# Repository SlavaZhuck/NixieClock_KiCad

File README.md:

# Clock on gas-discharge Nixie indicators  "IN-14" and Arduino
A fork of the adm503 project for those who want to be able to make changes to the circuit and/or board layout.
The circuit is copied with minimal changes (resistors, diode and transistor are changed to smd). The board and circuit are implemented in KiCad for 6 IN-14 lamps.<br>
The board has not been assembled and tested. It may not be. Please consider this information when using.<br>
The firmware has been updated to work with the DS3231M clock module.
The ability to automatically display data from the pressure, humidity and temperature sensor has been added.

Controls:
- When displaying the clock:
- M (double click) - enter the time settings mode;
- (hold) - enter the alarm settings mode;
- "minus" (short) - switches the lamp backlight modes;
- (hold) - enables/disables "glitches";
- "plus" (short) - switches the digit scrolling modes;
- (hold) - auto show temperature, pressure and humidity measurements
- sensor (short) - show temperature, pressure, humidity, set alarm time
(only if the alarm is on) and return to the clock display mode;
- (hold) - the same as (short).

- When the alarm goes off (a melody plays):
- sensor (short) - reset the signal, the alarm remains on;
- sensor (hold) - reset the signal, the alarm remains on.

- When displaying temperature, humidity, pressure, alarm time:
- sensor (short) - switch to the next parameter (pressure, humidity, set alarm time, clock display);
- (hold) - return to the clock display mode;

- When setting the time:
- M (short) - switch between setting hours and minutes;
- (hold) - reset the current group of digits to 00;
- "minus" (short) - decrease the value;
- (hold) - decrease the value by 5;
- "plus" (short) - increase the value;
- (hold) - increase the value by 5;
- sensor (short) - exit saving the settings;
- sensor (hold) - exit returning to the previous value.

- When setting the alarm:
- M (short) - switch between setting hours and minutes;
- (hold) - reset the current group of digits to 00;
- "minus" (short) - decrease the value;
- (hold) - decrease the value by 5;
- "plus" (short) - increase the value;
- (hold) - increase the value by 5;
- sensor (short) - exit with saving settings;
- sensor (hold) - turn on/off the alarm.

- Effects IN CLOCK MODE:
- Backlight (color changes cyclically: red, green, blue):
- Breathing;
- Constant glow;
- Disabled.
- Change digits (during change, the effect number is briefly displayed in all digits):
- (0) No effect;
- (1) Smooth fading;
- (2) Rewind in numerical order;
- (3) Rewind by cathodes;
- (4) Train;
- (5) Rubber band.
- The behavior of the second dot depends on whether the alarm is on? is set by the parameters:
- DOT_IN_TIME - when the alarm is off;
- DOT_IN_ALARM - when the alarm is on.
The dot behavior can be selected from the following values:
- DM_NULL, (0) the dot is always off;
- DM_ONCE, (1) the dot blinks once a second (normal);
- DM_HALF, (2) the dot changes brightness once a second;
- DM_TWICE, (3) the dot blinks twice a second;
- DM_THREE, (4) the dot blinks three times a second;
- DM_FULL, (5) the dot is always on

# Часы на газоразрядных индикаторах "ИН-14" и Arduino
Форк проекта adm503 для желающих иметь возможность сделать изменения в схеме и\или разводке платы.
Схема скопирована с минимальными изменениями (резисторы, диод и транзистор изменены на smd). Плата и схема реализованы в KiCad для 6-ти ламп ИН-14.<br>
Плата не была собрана и проверена. Возможно и не будет. Учитывайте пожалуйста эту информацию при использовании. <br>

Была обновлена прошивка для работы с модулем часов DS3231M.
Добавлена возможность автоматического показания данных с сенсора давления, влажности и температуры.
Управление:
  Управление:
  - При отображении часов:
    - М       (двойной клик) - войти в режим настроек времени;
    -         (удержание) - войти в режим настроек будильника;
    - "минус" (кратко) - переключает режимы подсветки ламп;
    -         (удержание) - включает/отключает "глюки";
    - "плюс"  (кратко) - переключает режимы перелистывания цифр;
    -         (удержание) - автопоказывать измерения температуры, давления и влажности
    - сенсор  (кратко) - показать температуру, давление, влажность, установленное время будильника
              (только если будильник включен) и вернуться в режим отображения часов;
    -         (удержание) - то же, что (кратко).
    
  - При срабатывании будильника (играет мелодия):
    - сенсор  (кратко) - сброс сигнала, будильник остаётся включенным;
    - сенсор  (удержание) - сброс сигнала, будильник остаётся включенным.
    
  - При демонстрации температуры, влажности, давлении, времени будильника:
    - сенсор  (кратко) - переключиться на следующий параметр (давление, влажность, установленное
              время будильника, отображение часов);
    -         (удержание) - вернуться в режим отображения часов;
    
  - При настройке времени:
    - М       (кратко) - переключение между установкой часов и минут;
    -         (удержание) - сброс текущей группы разрядов в 00;
    - "минус" (кратко) - уменьшение значения;
    -         (удержание) - уменьшение значения на 5;
    - "плюс"  (кратко) - увеличение значения;
    -         (удержание) - уведичение значения на 5;
    - сенсор  (кратко) - выход с сохранением установок;
    - сенсор  (удержание) - выход с возвратом к прежнему значению.
    
  - При настройке будильника:
    - М       (кратко) - переключение между установкой часов и минут;
    -         (удержание) - сброс текущей группы разрядов в 00;
    - "минус" (кратко) - уменьшение значения;
    -         (удержание) - уменьшение значения на 5;
    - "плюс"  (кратко) - увеличение значения;
    -         (удержание) - уведичение значения на 5;
    - сенсор  (кратко) - выход с сохранением установок;
    - сенсор  (удержание) - включение/выключение будильника.
    
  - Эффекты В РЕЖИМЕ ЧАСОВ:
    - Подсветка (циклически изменяется цвет: красный,  зелёный, синий):
      - Дыхание;
      - Постоянное свечение;
      - Отключена.
    - Смена цифр (при смене на короткое время отображается номер эффекта во всех разрядах):
      - (0) Без эффекта;
      - (1) Плавное угасание;
      - (2) Перемотка по порядку числа;
      - (3) Перемотка по катодам;
      - (4) Поезд;
      - (5) Резинка.
    - Поведение секундной точки зависит от того, включен ли будильник? устанавливается параметрами:
      - DOT_IN_TIME - когда будильник выключен;
      - DOT_IN_ALARM - когда будильник включен.
      Выбор поведения точки можно осуществлять из следующих величин:
      - DM_NULL, (0) точка постоянно выключена;
      - DM_ONCE, (1) точка моргает один раз в секунду (штатно);
      - DM_HALF, (2) точка изменяет яркость раз в секунду;
      - DM_TWICE,(3) точка моргает два раза в секунду;
      - DM_THREE,(4) точка моргает три раза в секунду;
      - DM_FULL, (5) точка постоянно включена

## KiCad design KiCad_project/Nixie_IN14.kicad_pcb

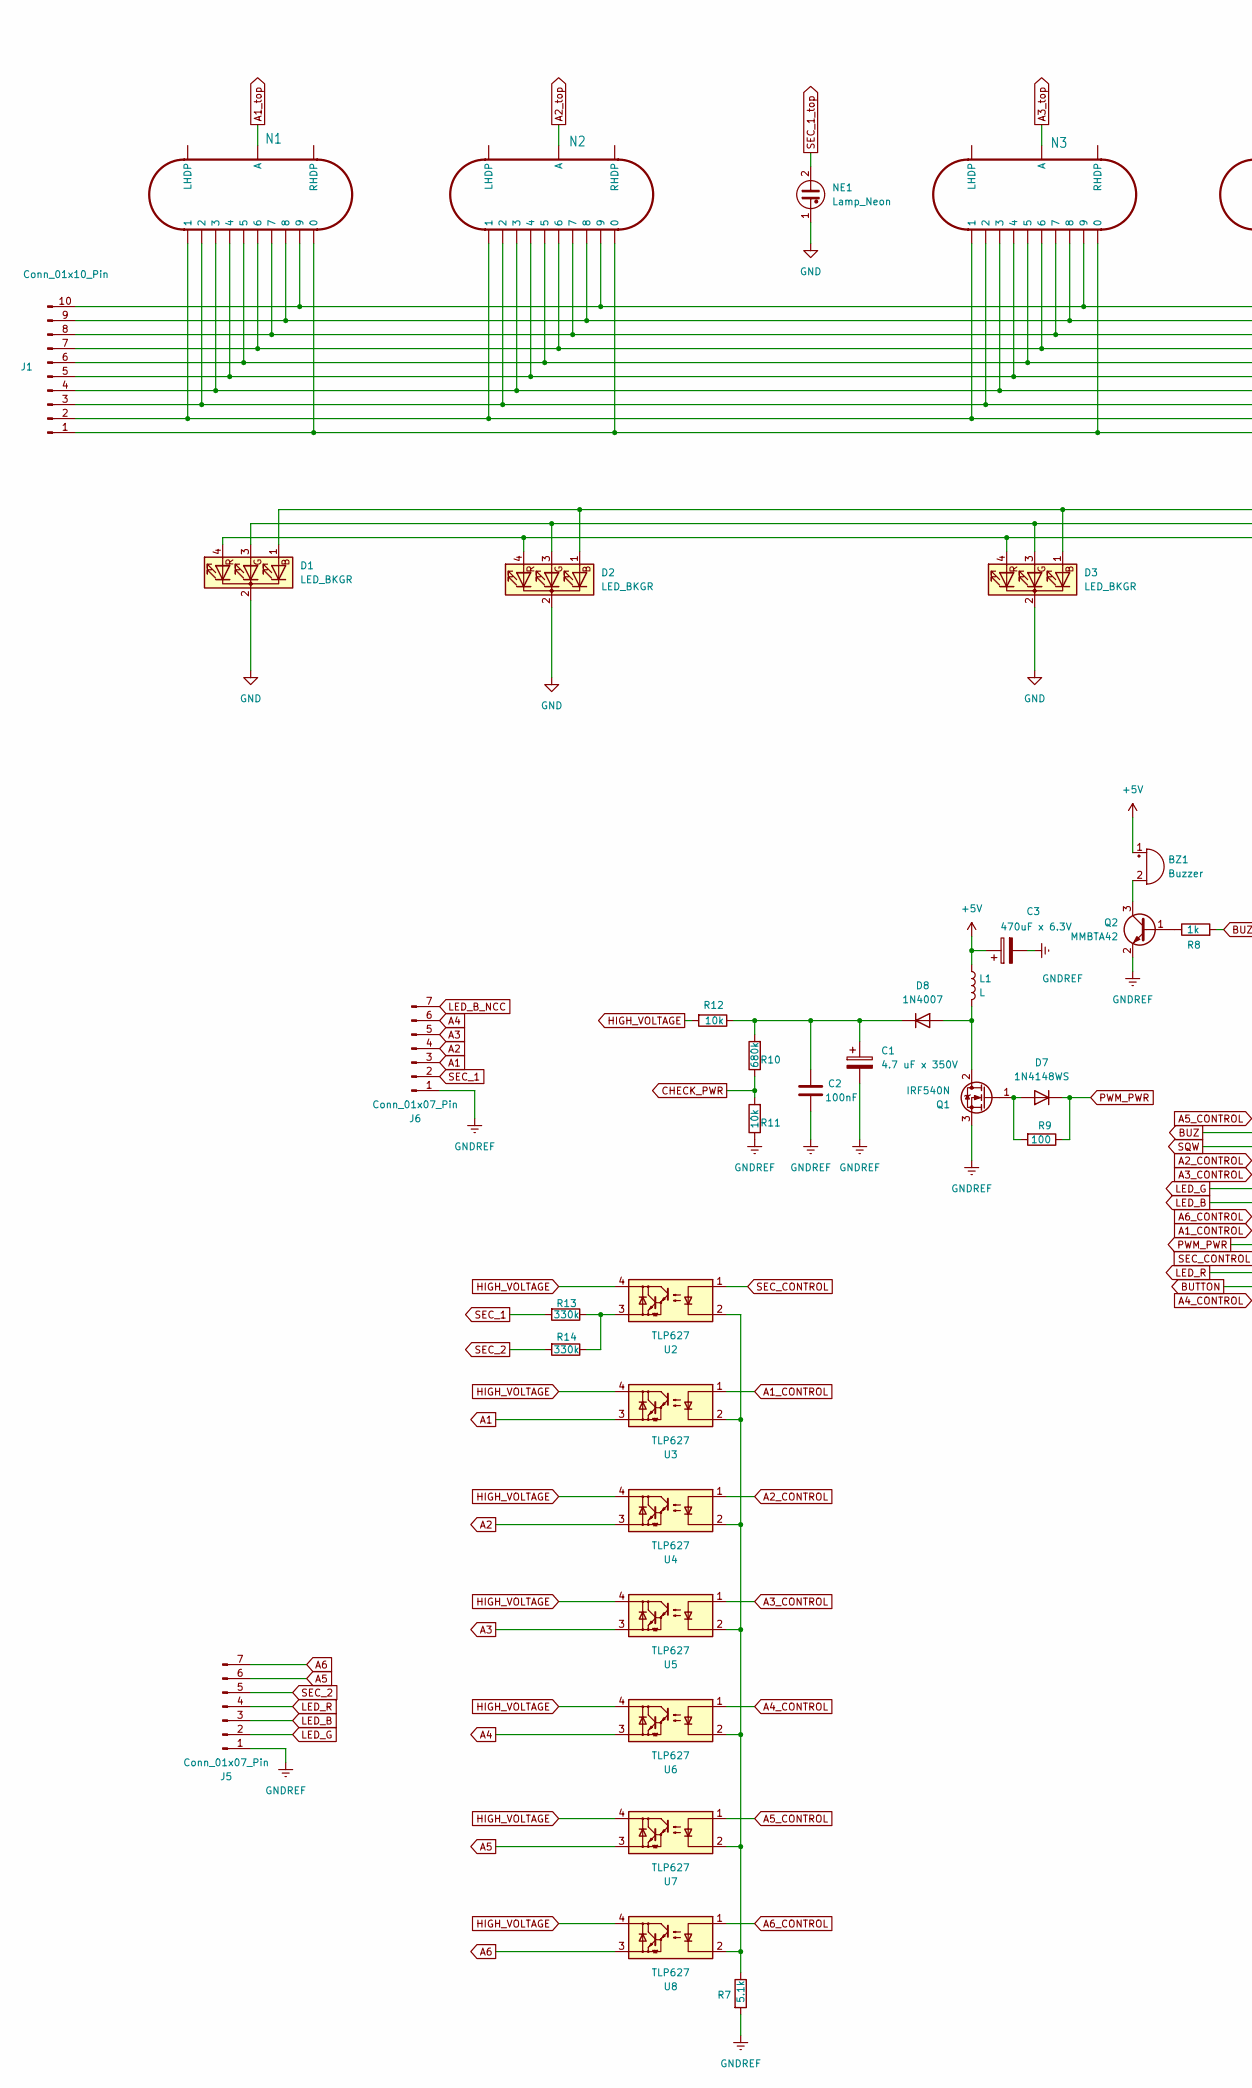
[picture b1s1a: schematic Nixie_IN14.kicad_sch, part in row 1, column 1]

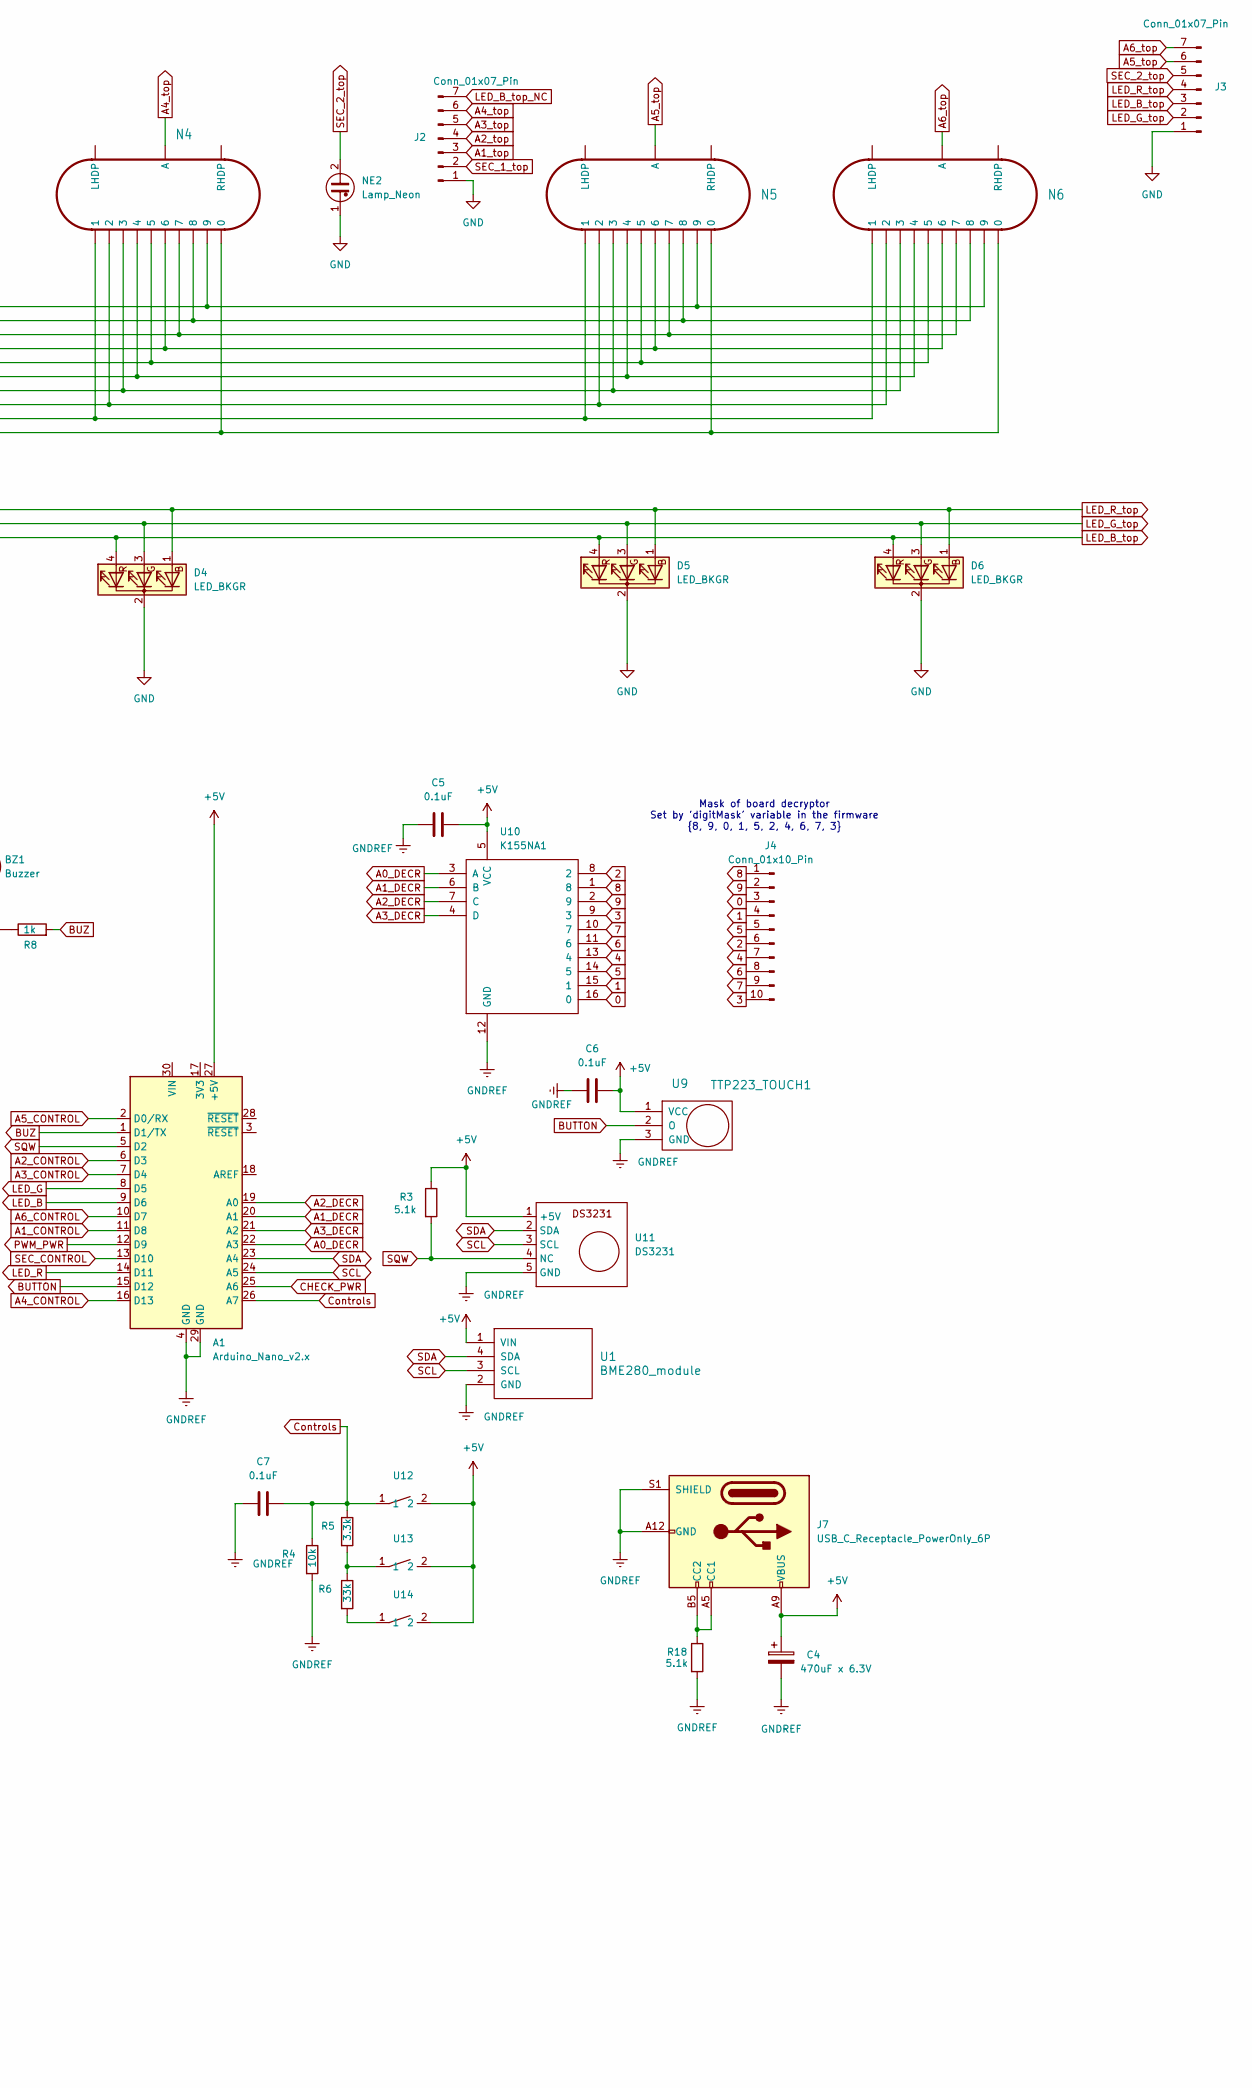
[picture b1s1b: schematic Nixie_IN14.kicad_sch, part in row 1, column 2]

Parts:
A1: Arduino_Nano_v2.x; Arduino_Nano
BZ1: Buzzer; Buzzer_TDK_PS1240P02BT_D12.2mm_H6.5mm
C1: 4.7 uF x 350V; CP_Radial_D10.0mm_P2.50mm_P5.00mm
C2: 100nF; C_Rect_L10.0mm_W5.0mm_P5.00mm_P7.50mm
C3, C4: 470uF x 6.3V; CP_Radial_D5.0mm_P2.50mm
C5, C6, C7: 0.1uF; C_1206_3216Metric
D1, D2, D3, D4, D5, D6: LED_BKGR; LED_D5.0mm-4_RGB
D7: 1N4148WS; D_SOD-323
D8: 1N4007; D_DO-41_SOD81_P7.62mm_Horizontal
J1: Conn_01x10_Pin; PinSocket_1x10_P2.54mm_Vertical
J2, J3: Conn_01x07_Pin; PinSocket_1x07_P2.54mm_Vertical
J4: Conn_01x10_Pin; PinHeader_1x10_P2.54mm_Vertical
J5, J6: Conn_01x07_Pin; PinHeader_1x07_P2.54mm_Vertical
J7: USB_C_Receptacle_PowerOnly_6P; USB_C_Receptacle_HRO_TYPE-C-31-M-17
L1: L; L_Radial_D10.0mm_P5.00mm_Fastron_07M
N1, N2, N3, N4, N5, N6: IN-14
NE1, NE2: Lamp_Neon; NE2-NEON-BULB-DRILL
Q1: IRF540N; TO-220-3_Vertical
Q2: MMBTA42; SOT-23
R3, R7, R18: 5.1k; R_1206_3216Metric_Pad1.30x1.75mm_HandSolder
R4, R11, R12: 10k; R_1206_3216Metric_Pad1.30x1.75mm_HandSolder
R5: 3.3k; R_1206_3216Metric_Pad1.30x1.75mm_HandSolder
R6: 33k; R_1206_3216Metric_Pad1.30x1.75mm_HandSolder
R8: 1k; R_1206_3216Metric_Pad1.30x1.75mm_HandSolder
R9: 100; R_1206_3216Metric_Pad1.30x1.75mm_HandSolder
R10: 680k; R_1206_3216Metric_Pad1.30x1.75mm_HandSolder
R13, R14: 330k; R_1206_3216Metric_Pad1.30x1.75mm_HandSolder
U1: BME280_module
U2, U3, U4, U5, U6, U7, U8: TLP627; DIP-4_W7.62mm
U9: TTP223_TOUCH1; PinHeader_1x03_P2.54mm_Vertical
U10: K155NA1; DIP-16_W7.62mm
U11: DS3231; DS3231_PI
U12, U13, U14: my_button

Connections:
0: J4.3, U10.16 (0)
1: J4.4, U10.15 (1)
2: J4.6, U10.8 (2)
3: J4.10, U10.9 (3)
4: J4.7, U10.13 (4)
5: J4.5, U10.14 (5)
6: J4.8, U10.11 (6)
7: J4.9, U10.10 (7)
8: J4.1, U10.1 (8)
9: J4.2, U10.2 (9)
+5V: A1.27 (+5V), BZ1.1 (+), C3.1, C4.1, C5.2, C6.2, J7.A9 (VBUS), J7.B9 (VBUS), L1.1, R3.1, U1.1 (VIN), U9.1 (VCC), U10.5 (VCC), U11.1 (+5V), U12.2, U13.2, U14.2
A0_DECR: A1.22 (A3), U10.3 (A)
A1: J6.3, U3.3
A1_CONTROL: A1.11 (D8), U3.1
A1_DECR: A1.20 (A1), U10.6 (B)
A1_top: J2.3, N1.A
A2: J6.4, U4.3
A2_CONTROL: A1.6 (D3), U4.1
A2_DECR: A1.19 (A0), U10.7 (C)
A2_top: J2.4, N2.A
A3: J6.5, U5.3
A3_CONTROL: A1.7 (D4), U5.1
A3_DECR: A1.21 (A2), U10.4 (D)
A3_top: J2.5, N3.A
A4: J6.6, U6.3
A4_CONTROL: A1.16 (D13), U6.1
A4_top: J2.6, N4.A
A5: J5.6, U7.3
A5_CONTROL: A1.2 (D0/RX), U7.1
A5_top: J3.6, N5.A
A6: J5.7, U8.3
A6_CONTROL: A1.10 (D7), U8.1
A6_top: J3.7, N6.A
BUTTON: A1.15 (D12), U9.2 (O)
BUZ: A1.1 (D1/TX), R8.2
CHECK_PWR: A1.25 (A6), R10.1, R11.2
Controls: A1.26 (A7), C7.1, R4.1, R5.1, U12.1
GND: D1.2 (K), D2.2 (K), D3.2 (K), D4.2 (K), D5.2 (K), D6.2 (K), J2.1, J3.1, NE1.1, NE2.1
GNDREF: A1.4 (GND), A1.29 (GND), C1.2, C2.2, C3.2, C4.2, C5.1, C6.1, C7.2, J5.1, J6.1, J7.A12 (GND), J7.B12 (GND), J7.S1 (SHIELD), Q1.3 (S), Q2.2 (E), R4.2, R7.2, R11.1, R18.2, U1.2 (GND), U9.3 (GND), U10.12 (GND), U11.5 (GND)
HIGH_VOLTAGE: R12.2, U2.4, U3.4, U4.4, U5.4, U6.4, U7.4, U8.4
LED_B: A1.9 (D6), J5.3
LED_B_NCC: J6.7
LED_B_top: D1.4 (RA), D2.4 (RA), D3.4 (RA), D4.4 (RA), D5.4 (RA), D6.4 (RA), J3.3
LED_B_top_NC: J2.7
LED_G: A1.8 (D5), J5.2
LED_G_top: D1.3 (GA), D2.3 (GA), D3.3 (GA), D4.3 (GA), D5.3 (GA), D6.3 (GA), J3.2
LED_R: A1.14 (D11), J5.4
LED_R_top: D1.1 (BA), D2.1 (BA), D3.1 (BA), D4.1 (BA), D5.1 (BA), D6.1 (BA), J3.4
unnamed: BZ1.2 (-), Q2.3 (C)
unnamed: D7.2 (A), Q1.1 (G), R9.2
unnamed: D8.2 (A), L1.2, Q1.2 (D)
unnamed: C1.1, C2.1, D8.1 (K), R10.2, R12.1
unnamed: J1.1, N1.0, N2.0, N3.0, N4.0, N5.0, N6.0
unnamed: J1.2, N1.1, N2.1, N3.1, N4.1, N5.1, N6.1
unnamed: J1.3, N1.2, N2.2, N3.2, N4.2, N5.2, N6.2
unnamed: J1.4, N1.3, N2.3, N3.3, N4.3, N5.3, N6.3
unnamed: J1.5, N1.4, N2.4, N3.4, N4.4, N5.4, N6.4
unnamed: J1.6, N1.5, N2.5, N3.5, N4.5, N5.5, N6.5
unnamed: J1.7, N1.6, N2.6, N3.6, N4.6, N5.6, N6.6
unnamed: J1.8, N1.7, N2.7, N3.7, N4.7, N5.7, N6.7
unnamed: J1.9, N1.8, N2.8, N3.8, N4.8, N5.8, N6.8
unnamed: J1.10, N1.9, N2.9, N3.9, N4.9, N5.9, N6.9
unnamed: J7.A5 (CC1), J7.B5 (CC2), R18.1
unnamed: Q2.1 (B), R8.1
unnamed: R5.2, R6.1, U13.1
unnamed: R6.2, U14.1
unnamed: R7.1, U2.2, U3.2, U4.2, U5.2, U6.2, U7.2, U8.2
unnamed: R13.1, R14.1, U2.3
PWM_PWR: A1.12 (D9), D7.1 (K), R9.1
SCL: A1.24 (A5), U1.3 (SCL), U11.3 (SCL)
SDA: A1.23 (A4), U1.4 (SDA), U11.2 (SDA)
SEC_1: J6.2, R13.2
SEC_1_top: J2.2, NE1.2
SEC_2: J5.5, R14.2
SEC_2_top: J3.5, NE2.2
SEC_CONTROL: A1.13 (D10), U2.1
SQW: A1.5 (D2), R3.2, U11.4 (NC)

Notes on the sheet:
Mask of board decryptor Set by 'digitMask' variable in the firmware {8, 9, 0, 1, 5, 2, 4, 6, 7, 3}

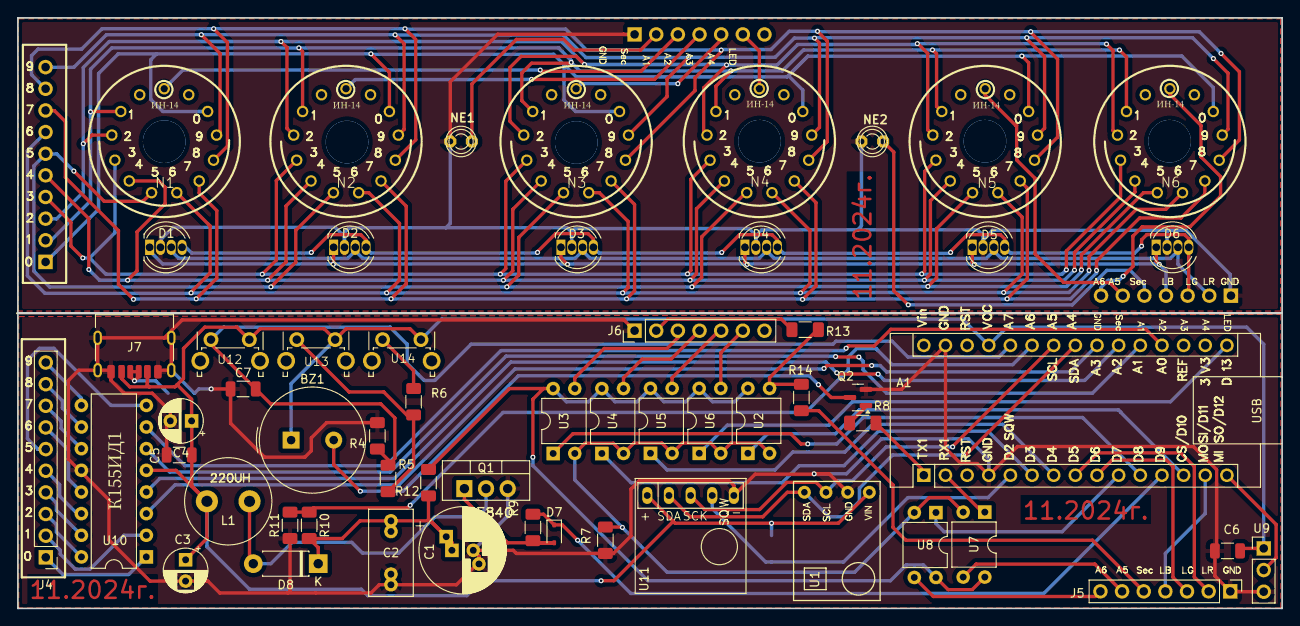
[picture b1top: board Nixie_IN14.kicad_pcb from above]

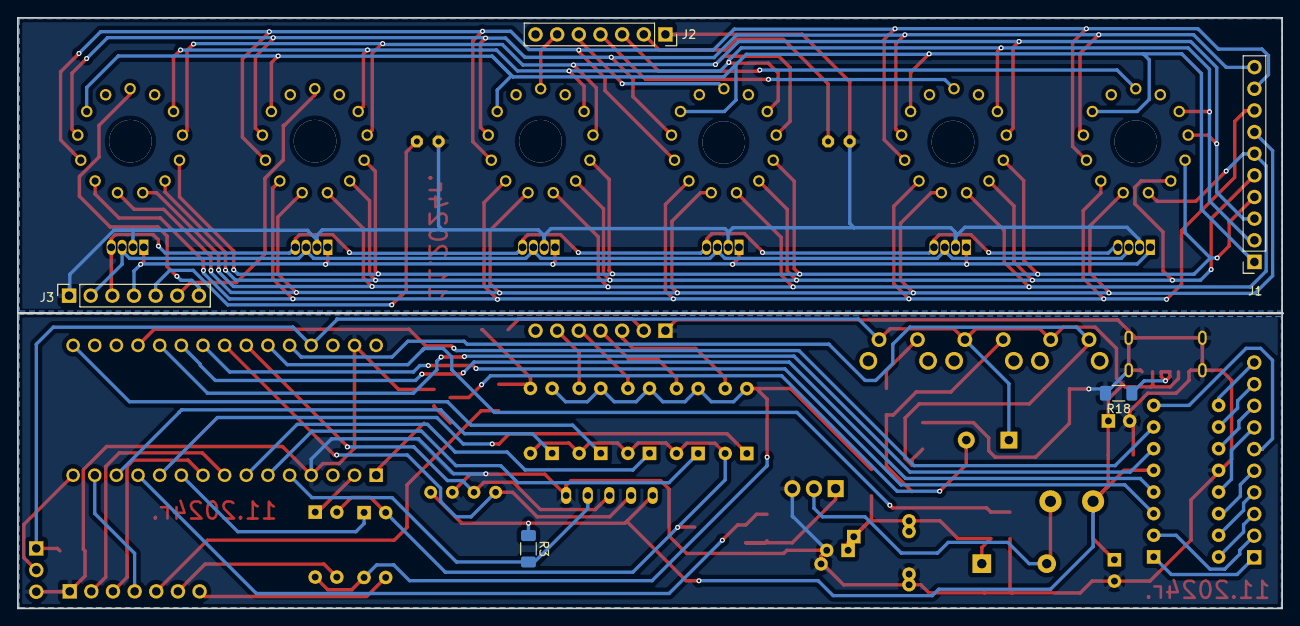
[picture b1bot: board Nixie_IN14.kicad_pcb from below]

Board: 2 copper layers, 148.3 x 69.3 mm, 62 parts (5 on the bottom side), 75 nets.

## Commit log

2021-10-11 Update LICENSE
2024-09-16 upload KiCad libraries PCB routing is not finished
2024-09-16 added missing lib
2024-09-16 added missed power capacitors fixed some resistor values continue placing elements on the PCB
2024-09-17 continue placing components
2024-09-17 placing and routing update
2024-09-18 optimized placement for tracing added labels on schematic added capacitor for button
2024-09-18 updated placement started routing
2024-09-19 placeng update first version of tracing is finished
2024-09-19 optimized routing and placement
2024-09-19 optimized placement and routing
2024-09-20 increased via diameters for drilling, routing optimization
2024-09-20 added 3d models
2024-09-21 placed transistors instead of optic pairs
2024-09-21 fixed connection error replaced and rerouted
2024-09-22 minor routing optimization
2024-09-22 added power keys for LEDs resistor pacjakges changed from 0805 to 1206
2024-11-02 DS3231SN switched to DS3231M,
    left only type 3 board support
2024-11-02 added periodic autoshow measurements with control from R-button (hold to turn On-Off) with saving to EEPROM
2024-11-06 decreased Voltage to 170 Volts, minor changes of brightness. Changed synchro mechanism for dynamic indication
2024-11-07 Added VScode project in "PlatformIO" extention
2024-11-08 git-annex in slava@slava-ThinkPad-E14-Gen-4-M:~/Documents/NixieClock_KiCad
2024-11-08 restored broken commit = updated placing of Arduino on PCB, optimized routing
2024-11-19 returned to D3231SN increased DOT brightness
2024-12-03 fixed compiler warnings updated time update process, each second data read from RTC updated auto show of measurements
2024-12-03 moved variable auto_show_measurements check to another unit
2024-12-03 only refactoring of brackets
2024-12-04 fixed burnIndicator and brightness usage
2024-12-04 refactor of effects file
2024-12-05 synchronized with Arduino project
2024-12-07 refactoring, split functions to separate files
2024-12-09 continue refactoring
2024-12-09 refactoring
2024-12-10 remove side effects
2024-12-28 refactor
2025-01-03 refactoring, changed interval to autoshow measurements
2025-01-19 updated DOT period and bright for res 5.1kOhm
2025-01-19 R7 changed from 510 to 5.1k
2025-01-21 update dot night brightness. Updated PCB for previous commit
2025-01-21 fix dot brightness for night
2025-02-02 change time calculation and synchro, change dot brightness
2025-02-02 fix formatting, no functional changes
2025-03-09 minor dot mode tuning
2026-05-27 added time adjustment to compensate quartz drift. Added possibility to set year, day and month
2026-05-28 # What changed Where 1 SETALARM hours/minutes adjust collapsed into bumpAlarm(delta, editingMins); fixed the copy-paste bug where btnR.isClick() was used twice instead of btnR.isHolded() for the +5 c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
2026-05-28 refactoring fix double extraction of startup_delay
2026-05-28 disable automatic backlight change during showing on measurements
2026-05-28 added setting for auto tuning time once per month fo defined amount of second forward or backward
